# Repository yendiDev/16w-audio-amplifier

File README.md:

# Simple 16W AB Class Audio Amplifier with TDA2030 IC

This project is a PCB design for an audio amplifier based on the TDA2030 integrated circuit. The TDA2030 is a low-frequency class AB amplifier known for its high output power and low harmonic distortion. This amplifier is designed to drive speakers with high efficiency and minimal distortion.

## Features

- **TDA2030 IC**: Provides high-fidelity audio amplification with low distortion.
- **Dual Power Supply**: Operates with a ±12V to ±18V power supply for optimal performance.
- **High Output Power**: Delivers up to 18W of continuous output power with proper heat dissipation.
- **Low Harmonic Distortion**: Ensures clear sound reproduction with minimal noise.
- **Screw Terminals**: Provided for secure speaker and power connections.
- **Capacitive Coupling**: Uses capacitors to block DC components and allow clean AC signal amplification.

## Components Used

- TDA2030 Integrated Circuit
- Electrolytic Capacitors (470µF, 1000µF, etc.)
- Ceramic Capacitors (0.1µF, 100nF)
- Resistors (1Ω, 4.7Ω, 100kΩ, etc.)
- Diodes (1N4007)

## Circuit Design

The circuit is designed to amplify audio signals while ensuring stability and protection. It follows a standard class AB configuration with a split power supply. The input signal passes through a coupling capacitor to prevent DC offset. The feedback network is optimized for gain control and frequency response.

## Applications

- DIY audio amplifier projects
- Speaker enhancement systems
- Home theater audio setups
- Subwoofer amplifiers

### Schematics:

### PCB Layout:
Front layer:

Bottom layer:

### 3D view of PCB:

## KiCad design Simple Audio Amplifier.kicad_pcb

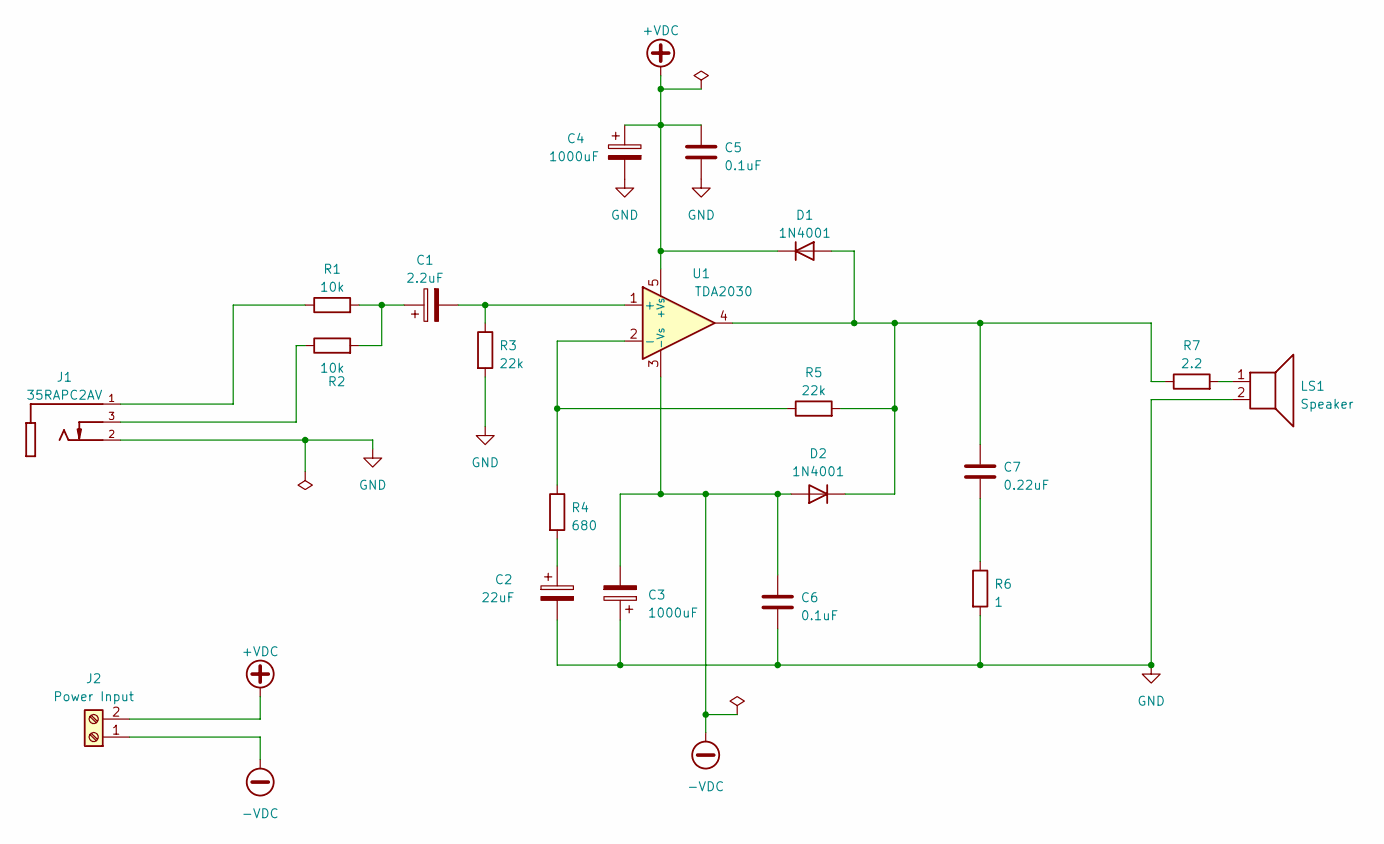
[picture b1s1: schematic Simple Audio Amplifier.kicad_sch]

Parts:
C1: 2.2uF; CP_Axial_L10.0mm_D4.5mm_P15.00mm_Horizontal
C2: 22uF; CP_Axial_L10.0mm_D4.5mm_P15.00mm_Horizontal
C3, C4: 1000uF; CP_Axial_L10.0mm_D4.5mm_P15.00mm_Horizontal
C5, C6: 0.1uF; CP_Axial_L10.0mm_D4.5mm_P15.00mm_Horizontal
C7: 0.22uF; CP_Axial_L10.0mm_D4.5mm_P15.00mm_Horizontal
D1, D2: 1N4001; D_DO-41_SOD81_P10.16mm_Horizontal
J1: 35RAPC2AV; SWITCHCRAFT_35RAPC2AV; PARTREV B; DigiKey_Part_Number SC1457-ND
J2: Power Input; TerminalBlock_Phoenix_MKDS-1,5-2-5.08_1x02_P5.08mm_Horizont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
LS1: Speaker; TerminalBlock_Phoenix_MKDS-1,5-2-5.08_1x02_P5.08mm_Horizont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
R1, R2: 10k; R_Axial_DIN0204_L3.6mm_D1.6mm_P5.08mm_Horizontal
R3, R5: 22k; R_Axial_DIN0204_L3.6mm_D1.6mm_P5.08mm_Horizontal
R4: 680; R_Axial_DIN0204_L3.6mm_D1.6mm_P5.08mm_Horizontal
R6: 1; R_Axial_DIN0204_L3.6mm_D1.6mm_P5.08mm_Horizontal
R7: 2.2; R_Axial_DIN0204_L3.6mm_D1.6mm_P5.08mm_Horizontal
U1: TDA2030; TO-220-5_P3.4x3.7mm_StaggerOdd_Lead3.8mm_Vertical

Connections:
+VDC: C4.1, C5.1, D1.1 (K), J2.2, U1.5 (+Vs)
-VDC: C3.2, C6.1, D2.2 (A), J2.1, U1.3 (-Vs)
GND: C2.2, C3.1, C4.2, C5.2, C6.2, J1.2, LS1.2, R3.2, R6.2
unnamed: C1.1, R1.2, R2.2
unnamed: C2.1, R4.2
unnamed: C7.2, R6.1
unnamed: C7.1, D1.2 (A), D2.1 (K), R5.2, R7.1, U1.4
unnamed: J1.1, R1.1
unnamed: J1.3, R2.1
unnamed: LS1.1, R7.2
unnamed: C1.2, R3.1, U1.1 (+)
unnamed: R4.1, R5.1, U1.2 (-)

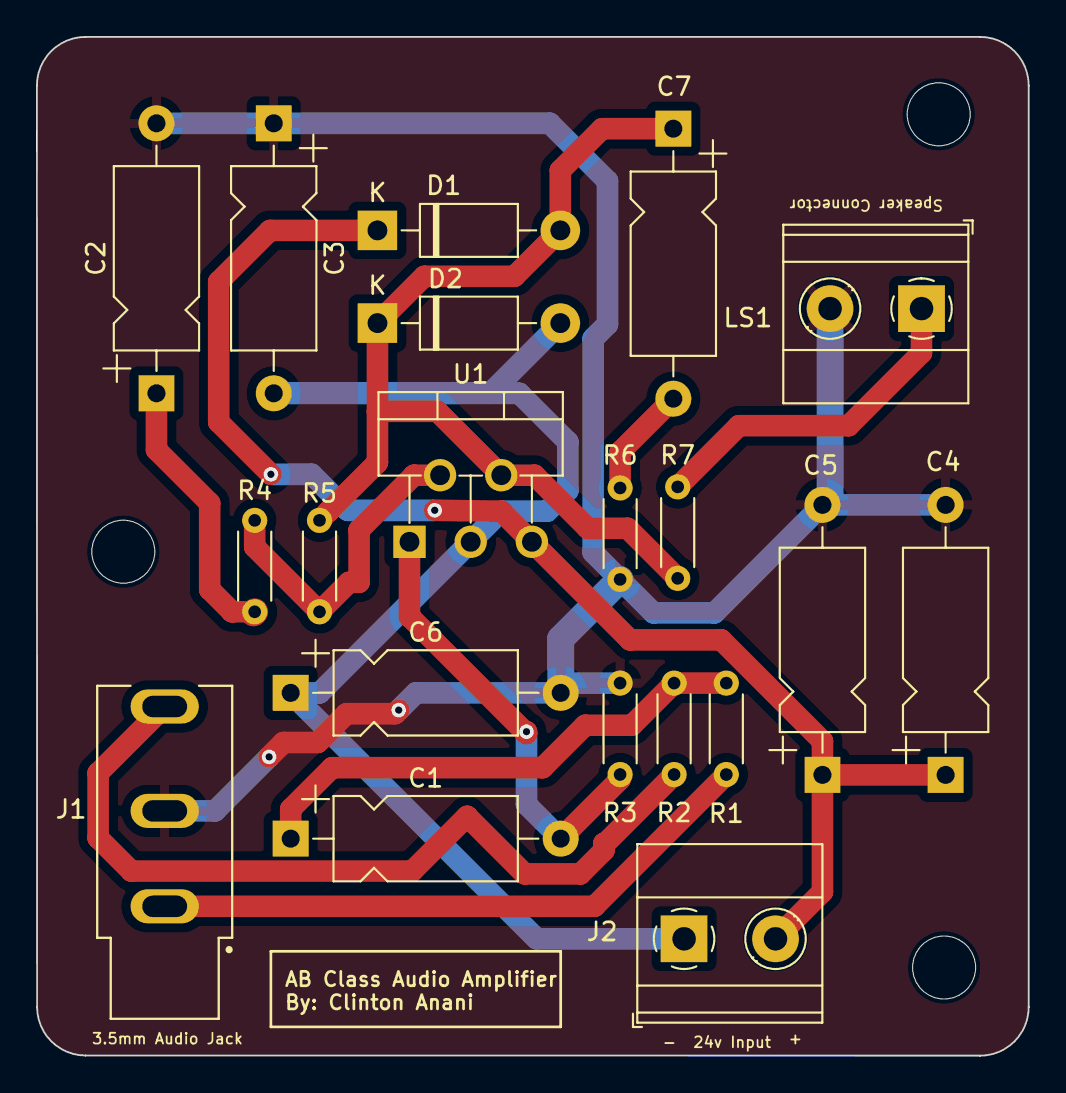
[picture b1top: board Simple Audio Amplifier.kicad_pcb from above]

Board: 2 copper layers, 55.1 x 56.6 mm, 20 parts (0 on the bottom side), 12 nets.
